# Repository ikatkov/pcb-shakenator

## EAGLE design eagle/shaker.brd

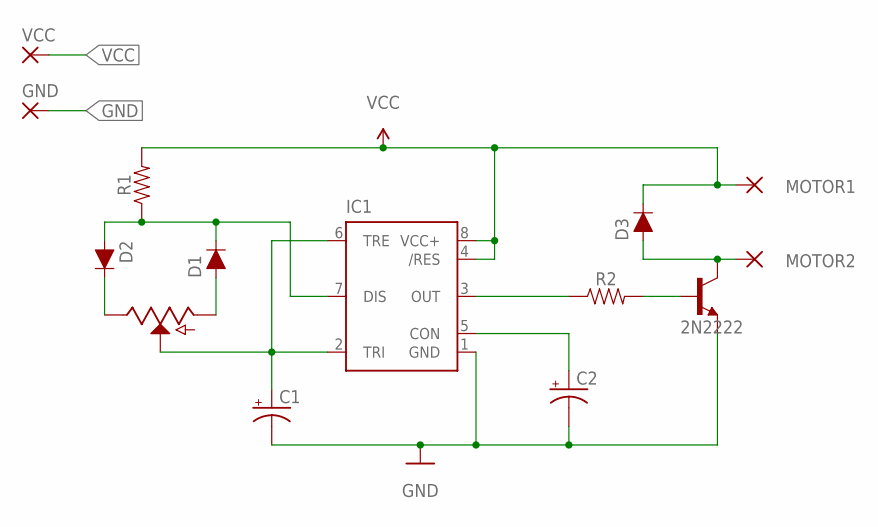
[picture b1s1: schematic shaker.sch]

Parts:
2N2222: 200mA/40V; TO-92
C1: CAPACITOR_5MM; CAPPRD508W65D500H1100B
C2: 100nF; CAPPRD508W65D500H1100B
D1, D2, D3: DIODEDEFAULT; DIODE
GND: 3,81/1,4
IC1: 555; DIP8
MOTOR1, MOTOR2: 3,81/1,4
R1: RESISTORDEFAULT; RESISTOR
R2: 1k; RESISTOR
VCC: 3,81/1,4
VR1: 10k; POTENTIOMETER

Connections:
CON: C2.1 (+), IC1.5 (CON)
DIS: D1.CATHODE (C), D2.ANODE (A), IC1.7 (DIS), R1.1
GND: 2N2222.1 (E), C1.2 (-), C2.2 (-), GND.1, IC1.1 (GND)
MOTOR2: 2N2222.3 (C), D3.ANODE (A), MOTOR2.1
unnamed: 2N2222.2 (B), R2.2
unnamed: D2.CATHODE (C), VR1.B (E)
unnamed: D1.ANODE (A), VR1.A
OUT: IC1.3 (OUT), R2.1
TRI: C1.1 (+), IC1.2 (TRI), IC1.6 (TRE), VR1.C (CENTER)
VCC: D3.CATHODE (C), IC1.4 (/RES), IC1.8 (VCC+), MOTOR1.1, R1.2, VCC.1

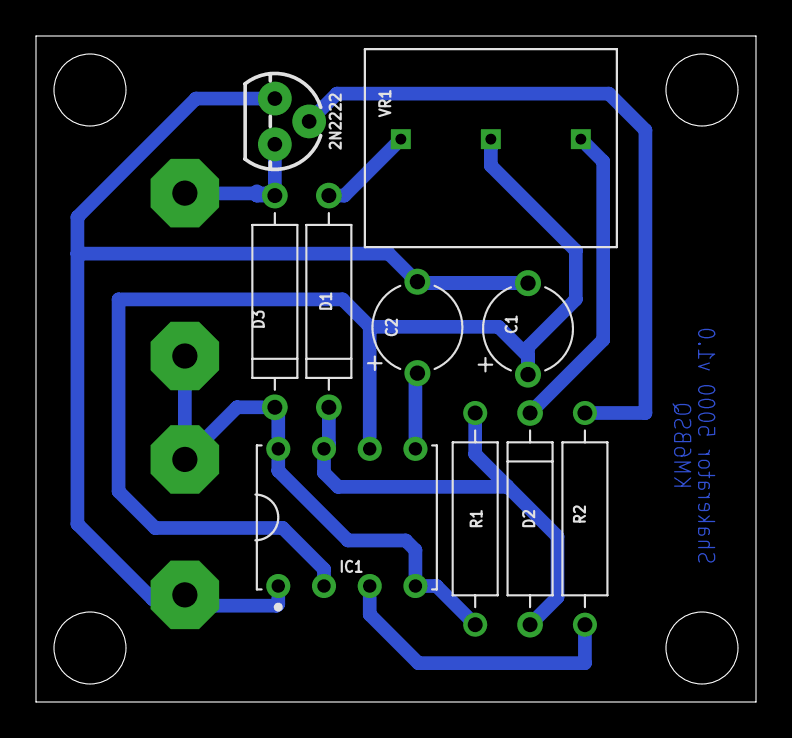
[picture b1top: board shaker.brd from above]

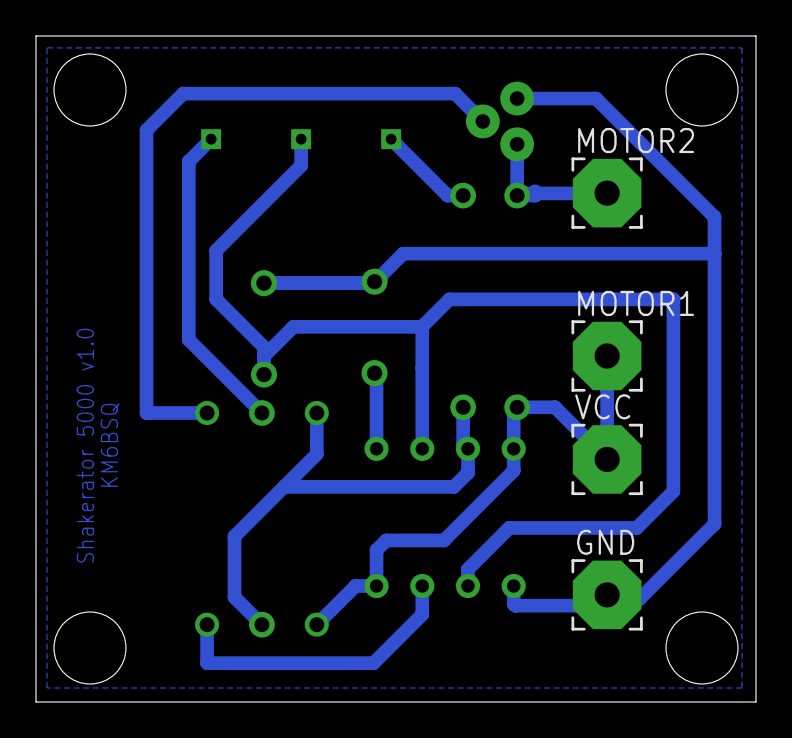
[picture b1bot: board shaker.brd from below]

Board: 2 copper layers, 40.0 x 37.0 mm, 14 parts (4 on the bottom side), 10 nets.

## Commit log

2020-11-01 3d-printed enclosure
2020-11-01 All images

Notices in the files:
parts and their libraries:
SparkFun-PowerSymbols: Licensing: Creative Commons ShareAlike 4.0 International - https://creativecommons.org/licenses/by-sa/4.0
